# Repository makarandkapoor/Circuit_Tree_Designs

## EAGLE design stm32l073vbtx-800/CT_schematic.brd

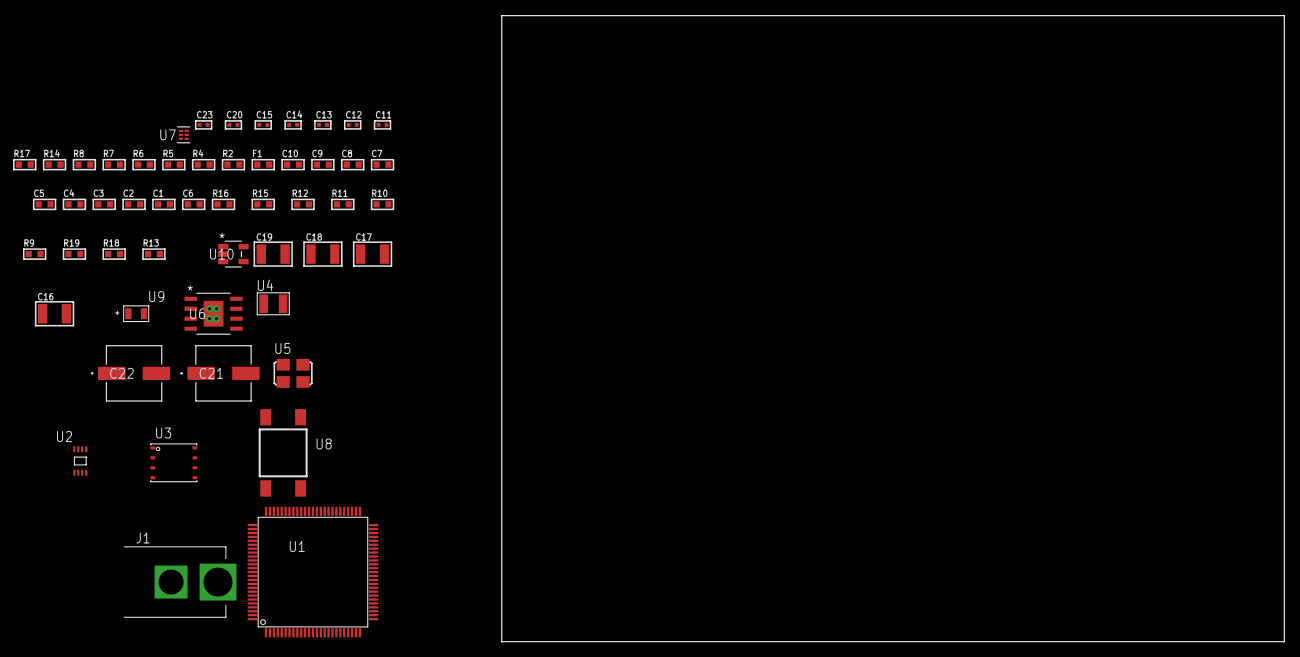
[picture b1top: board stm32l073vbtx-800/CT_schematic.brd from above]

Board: 2 copper layers, 100.0 x 80.0 mm, 52 parts (0 on the bottom side), 23 nets, no tracks yet.

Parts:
C1, C2, C3, C4, C5, C7, C10: 1e-07; C0603
C6: 4.7e-06; C0603
C8: 1e-08; C0603
C9: 1e-06; C0603
C11, C12: 1e-11; C0402
C13, C14, C15, C23: 1e-08; C0402
C16, C17, C18, C19: 1e-05; C1210
C20: 1e-07; C0402
C21, C22: 0.0001; EXV-9H
F1: 240.0; L0603
J1: PJ-037B; PJ-037B_PACKAGE
R2: 1000.0; R0603
R4: 4700.0; R0603
R5, R6, R7, R8, R14: 2200.0; R0603
R9, R10, R11, R12, R15, R16: 10000.0; R0603
R13: 4031.5447154472; R0603
R17: 9100.0; R0603
R18: 680000.0; R0603
R19: 120000.0; R0603
U1: STM32L073VBT6; LQFP100
U2: 24AA04-I/MC; TDFN-8/6MM
U3: 24AA256-I/MF; DFN8-S
U4: ABS07-32.768KHZ-7-T
U5: ASFL1-25MHZ-NCS; ASFL1
U6: MIC5234YME; SOIC-8_EP
U7: TPS3895ADRYR; SON-6
U8: 4-1437565-2; SW_4-1437565-2
U9: Q65110A2395; LGM67K-G1J2-24-Z
U10: nc7sz125m5x; NC7SZ125M5X

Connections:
CLK_CRYSTAL_U1_8: C11.1, U1.8, U4.1
CLK_CRYSTAL_U1_9: C12.1, U1.9, U4.2
CLK_U1_12: U1.12, U5.3
GND: C1.2, C2.2, C3.2, C4.2, C5.2, C6.2, C7.2, C8.2, C9.2, C10.2, C11.2, C12.2, C13.2, C14.2, C15.2, C16.2, C17.2, C18.2, C19.2, C20.2, C21.2, C22.2, C23.2, J1.2, R2.2, R9.2, R10.2, R12.2, R14.2, R17.2, R19.2, U1.19, U1.20, U1.27, U1.49, U1.74, U1.99, U2.4, U3.4, U5.2, U6.7, U6.EPAD, U7.2, U9.C, U10.1, U10.3
NET_U1_6: C7.1, U1.6
NET_U1_14: R4.1, U1.14, U10.4
NET_U1_22: C8.1, C9.1, F1.1, U1.21, U1.22
NET_U1_47: R7.1, U1.47, U2.6
NET_U1_48: R8.1, U1.48, U2.5
NET_U1_68: R5.1, U1.68, U3.6
NET_U1_69: R6.1, U1.69, U3.5
NET_U1_94: R9.1, U1.94
NET_U1_98: U8.3, U8.4
NET_U3_1: R10.1, U3.1
NET_U3_2: R11.1, U3.2
NET_U3_3: R12.1, U3.3
NET_U6_4: R13.2, R14.1, U6.4
NET_U7_1: R16.1, R17.1, U7.1
NET_U7_3: R18.2, R19.1, U7.3
NET_U7_4: R15.1, U7.4, U10.2
NET_U8_1: R2.1, U8.1, U8.2
VCC_S1_13V7: C16.1, C17.1, C21.1, C22.1, J1.1, U6.5, U6.8
VCC_TIER1_3V3: C1.1, C2.1, C3.1, C4.1, C5.1, C6.1, C10.1, C13.1, C14.1, C15.1, C18.1, C19.1, C20.1, C23.1, F1.2, R4.2, R5.2, R6.2, R7.2, R8.2, R11.2, R13.1, R15.2, R16.2, R18.1, U1.28, U1.50, U1.73, U1.75, U1.100, U2.7, U2.8, U3.7, U3.8, U5.4, U6.1, U7.6, U10.5

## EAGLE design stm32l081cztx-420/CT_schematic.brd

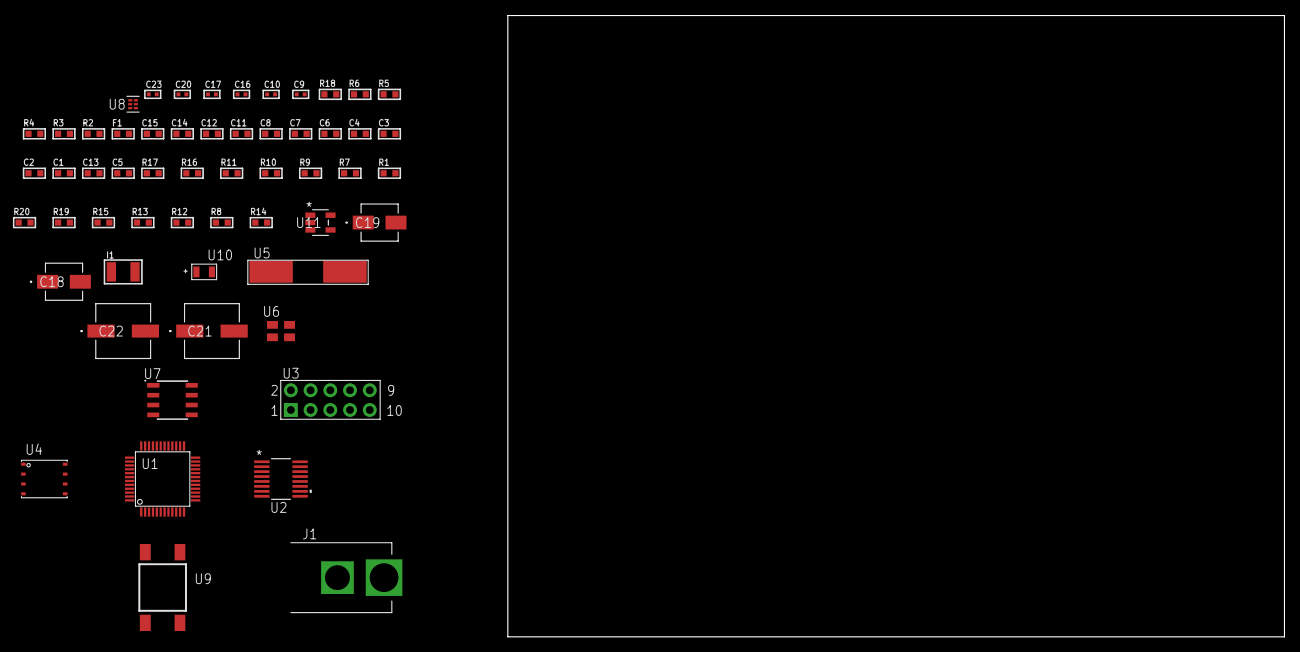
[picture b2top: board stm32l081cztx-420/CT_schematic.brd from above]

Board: 2 copper layers, 100.0 x 80.0 mm, 57 parts (0 on the bottom side), 36 nets, no tracks yet.

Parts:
C1, C2, C3, C4, C6: 1e-07; C0603
C5: 4.7e-06; C0603
C7: 1e-08; C0603
C8, C11, C12, C14, C15: 1e-06; C0603
C9, C10: 1e-11; C0402
C13: 2.2e-07; C0603
C16, C17, C23: 1e-08; C0402
C18: 1e-06; EXV-9B
C19: 2.2e-06; EXV-9B
C20: 1e-07; C0402
C21, C22: 0.0001; EXV-9H
F1: 240.0; L0603
I1: 1e-05; L1210
J1: PJ-037B; PJ-037B_PACKAGE
R1, R7, R9, R10, R11, R16, R17: 10000.0; R0603
R2: 1000.0; R0603
R3: 1600.5; R0603
R4: 4700.0; R0603
R5, R6: 2200.0; R0603
R8, R12, R13, R15: 100000.0; R0603
R14: 164658.62; R0603
R18: 9100.0; R0603
R19: 680000.0; R0603
R20: 120000.0; R0603
U1: STM32L081CZT6; LQFP48
U2: LTC2804CGN-1#PBF; SSOP-16
U3: HTSS-105-01-G-D
U4: 24AA256-I/MF; DFN8-S
U5: ABLS-25.000MHZ-B2F-T
U6: ASEK-32.768KHz-ECST; ASEK
U7: LP2954AIMX/NOPB; LP2954
U8: TPS3895ADRYR; SON-6
U9: 4-1437565-2; SW_4-1437565-2
U10: Q65110A2395; LGM67K-G1J2-24-Z
U11: nc7sz125m5x; NC7SZ125M5X

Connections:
CLK_CRYSTAL_U1_5: C9.1, U1.5, U5.1
CLK_CRYSTAL_U1_6: C10.1, U1.6, U5.2
CLK_U1_3: U1.3, U6.3
GND: C1.2, C2.2, C3.2, C4.2, C5.2, C6.2, C7.2, C8.2, C9.2, C10.2, C11.2, C12.2, C14.2, C15.2, C16.2, C17.2, C18.2, C19.2, C20.2, C21.2, C22.2, C23.2, J1.2, R2.2, R7.2, R9.2, R10.2, R15.2, R18.2, R20.2, U1.8, U1.23, U1.35, U1.47, U2.8, U3.9, U4.4, U6.2, U7.4, U8.2, U10.C, U11.1, U11.3
NET_U1_7: R4.1, U1.7, U11.4
NET_U1_9: C7.1, C8.1, F1.1, U1.9
NET_U1_30: R5.1, U1.30, U4.6
NET_U1_31: R6.1, U1.31, U4.5
NET_U1_44: R7.1, U1.44
NET_U1_45: R3.1, U1.45, U10.A
NET_U1_46: R1.1, U1.46, U9.3, U9.4
NET_U2_6: C11.1, U2.6
NET_U2_7: C13.1, I1.2, U2.7
NET_U2_9: C12.1, U2.9
NET_U2_10: C13.2, U2.10
NET_U2_11: R8.1, U2.11
NET_U3_3: U2.1, U3.3
NET_U3_4: U2.2, U3.4
NET_U3_5: U2.3, U3.5
NET_U3_6: U2.4, U3.6
NET_U4_1: R9.1, U4.1
NET_U4_2: R10.1, U4.2
NET_U4_3: R11.1, U4.3
NET_U7_3: R13.1, U7.3
NET_U7_5: R12.1, U7.5
NET_U7_7: R14.2, R15.1, U7.7
NET_U8_1: R17.1, R18.1, U8.1
NET_U8_3: R19.2, R20.1, U8.3
NET_U8_4: R16.1, U8.4, U11.2
NET_U9_1: R2.1, U9.1, U9.2
PROC_LPUART1_CTS: U1.16, U2.13
PROC_LPUART1_RTS: U1.19, U2.15
PROC_LPUART1_RX: U1.13, U2.16
PROC_LPUART1_TX: U1.12, U2.14
VCC_S1_16V4: C18.1, C21.1, C22.1, J1.1, R13.2, U7.8
VCC_TIER1_3V3: C1.1, C2.1, C3.1, C4.1, C5.1, C6.1, C14.1, C15.1, C16.1, C17.1, C19.1, C20.1, C23.1, F1.2, I1.1, R1.2, R3.2, R4.2, R5.2, R6.2, R8.2, R11.2, R12.2, R14.1, R16.2, R17.2, R19.1, U1.1, U1.24, U1.36, U1.48, U2.5, U2.12, U4.7, U4.8, U6.4, U7.1, U8.6, U11.5

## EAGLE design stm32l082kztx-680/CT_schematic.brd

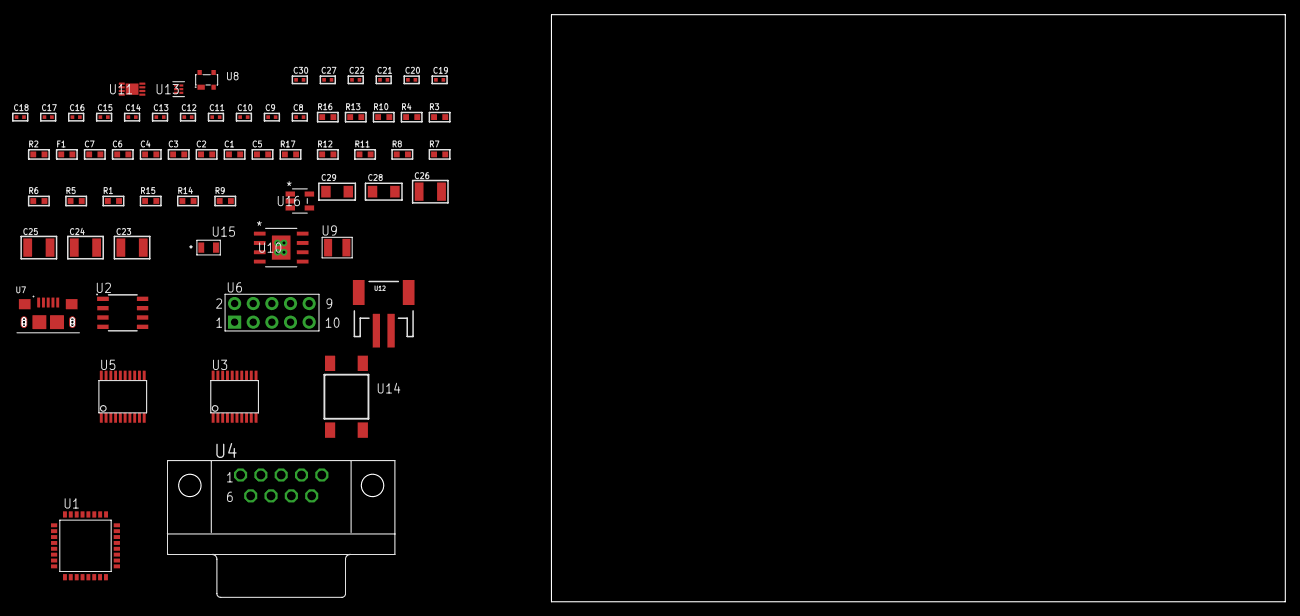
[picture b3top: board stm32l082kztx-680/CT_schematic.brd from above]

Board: 2 copper layers, 172.1 x 80.0 mm, 64 parts (0 on the bottom side), 54 nets, no tracks yet.

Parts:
C1, C2, C3, C4: 1e-07; C0603
C5: 4.7e-06; C0603
C6: 1e-08; C0603
C7: 1e-06; C0603
C8, C9: 1e-11; C0402
C10, C30: 1e-08; C0402
C11, C12, C13, C14, C15, C16, C17, C18, C19, C20, C21, C22, C27: 1e-07; C0402
C23, C24, C25, C26: 1e-05; C1210
C28, C29: 1e-05; C1206
F1: 240.0; L0603
R1, R5, R6, R7, R8, R11, R12, R17: 10000.0; R0603
R2: 1000.0; R0603
R3: 1600.5; R0603
R4: 4700.0; R0603
R9: 4031.5447154472; R0603
R10: 2200.0; R0603
R13: 9100.0; R0603
R14: 680000.0; R0603
R15: 120000.0; R0603
R16: 2000.0; R0603
U1: STM32L082KZT6; LQFP32
U2: AT25020B-SSHL-T; SOIC-8
U3, U5: SP3203ECY-L/TR; TSSOP20-I
U4: 182-009-113R531; 182-009-MALE
U6: HTSS-105-01-G-D
U7: 10118193-0001LF; FCI_10118193-0001LF
U8: prtr5v0u2ax; SOT143B
U9: ABS07-32.768KHZ-7-T
U10: MIC5234YME; SOIC-8_EP
U11: MCP73831T-2ACI/MC; DFN8_2X3MC
U12: S2B-PH-SM4-TB(LF)(SN); JST-2-SMD
U13: TPS3895ADRYR; SON-6
U14: 4-1437565-2; SW_4-1437565-2
U15: Q65110A2395; LGM67K-G1J2-24-Z
U16: nc7sz125m5x; NC7SZ125M5X

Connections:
CLK_CRYSTAL_U1_2: C8.1, U1.2, U9.1
CLK_CRYSTAL_U1_3: C9.1, U1.3, U9.2
GND: C1.2, C2.2, C3.2, C4.2, C5.2, C6.2, C7.2, C8.2, C9.2, C10.2, C11.2, C12.2, C15.2, C16.2, C17.2, C18.2, C21.2, C22.2, C23.2, C24.2, C25.2, C26.2, C27.2, C28.2, C29.2, C30.2, R2.2, R5.2, R10.2, R13.2, R15.2, R16.2, U1.16, U1.32, U2.4, U3.18, U4.5, U5.18, U6.9, U7.5, U7.6, U7.7, U7.8, U7.9, U8.1, U10.7, U10.EPAD, U11.6, U11.9, U12.2, U13.2, U15.C, U16.1, U16.3
INPUT_USBPOWER_5V: C28.1, R17.2, U7.1, U8.4, U11.1, U11.2
NET_U1_4: R4.1, U1.4, U16.4
NET_U1_5: C6.1, C7.1, F1.1, U1.5
NET_U1_29: R3.1, U1.29, U15.A
NET_U1_30: R1.1, U1.30, U14.3, U14.4
NET_U1_31: R5.1, U1.31
NET_U2_3: R6.1, U2.3
NET_U2_7: R8.1, U2.7
NET_U3_1: C13.1, U3.1
NET_U3_2: C15.1, U3.2
NET_U3_3: C13.2, U3.3
NET_U3_4: C14.1, U3.4
NET_U3_5: C14.2, U3.5
NET_U3_6: C16.1, U3.6
NET_U4_2: U3.14, U4.2
NET_U4_3: U3.17, U4.3
NET_U4_7: U3.13, U4.7
NET_U4_8: U3.16, U4.8
NET_U5_1: C19.1, U5.1
NET_U5_2: C21.1, U5.2
NET_U5_3: C19.2, U5.3
NET_U5_4: C20.1, U5.4
NET_U5_5: C20.2, U5.5
NET_U5_6: C22.1, U5.6
NET_U6_3: U5.14, U6.3
NET_U6_4: U5.13, U6.4
NET_U6_5: U5.17, U6.5
NET_U6_6: U5.16, U6.6
NET_U10_4: R9.2, R10.1, U10.4
NET_U11_5: R17.1, U11.5
NET_U11_8: R16.1, U11.8
NET_U13_1: R12.1, R13.1, U13.1
NET_U13_3: R14.2, R15.1, U13.3
NET_U13_4: R11.1, U13.4, U16.2
NET_U14_1: R2.1, U14.1, U14.2
PROC_LPUART1_CTS: U1.12, U3.8
PROC_LPUART1_RTS: U1.15, U3.10
PROC_LPUART1_RX: U1.9, U3.11
PROC_LPUART1_TX: U1.8, U3.7
PROC_SPI1_MISO: U1.27, U2.2
PROC_SPI1_MOSI: U1.13, U2.5
PROC_SPI1_NSS: R7.1, U1.10, U2.1
PROC_SPI1_SCK: U1.11, U2.6
PROC_USART2_CTS: U1.6, U5.8
PROC_USART2_RTS: U1.7, U5.10
PROC_USART2_RX: U1.25, U5.11
PROC_USART2_TX: U1.24, U5.7
PROC_USB_DM: U1.21, U7.2, U8.3
PROC_USB_DP: U1.22, U7.3, U8.2
VCC_S1_3V7: C23.1, C24.1, C29.1, U10.5, U10.8, U11.3, U11.4, U12.1
VCC_TIER1_3V3: C1.1, C2.1, C3.1, C4.1, C5.1, C10.1, C11.1, C12.1, C17.1, C18.1, C25.1, C26.1, C27.1, C30.1, F1.2, R1.2, R3.2, R4.2, R6.2, R7.2, R8.2, R9.1, R11.2, R12.2, R14.1, U1.1, U1.17, U2.8, U3.12, U3.19, U5.12, U5.19, U10.1, U13.6, U16.5

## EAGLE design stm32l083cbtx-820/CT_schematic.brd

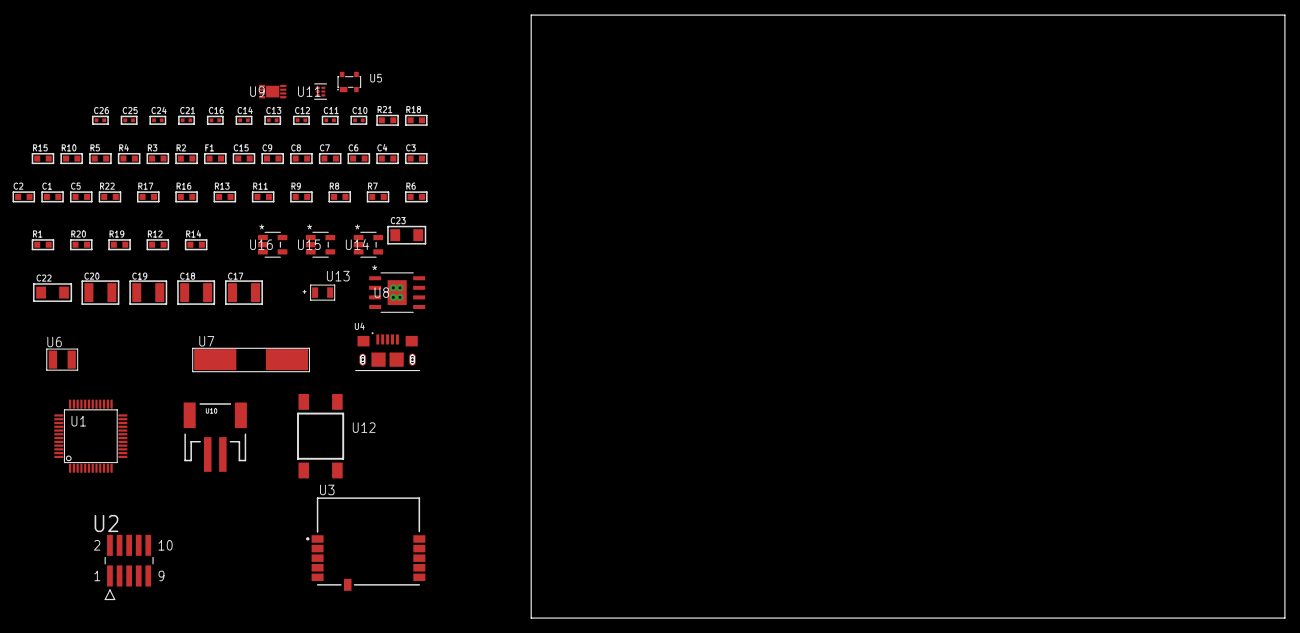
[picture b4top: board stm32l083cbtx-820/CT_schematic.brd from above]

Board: 2 copper layers, 122.6 x 80.0 mm, 65 parts (0 on the bottom side), 33 nets, no tracks yet.

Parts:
C1, C2, C3, C4, C6, C9: 1e-07; C0603
C5: 4.7e-06; C0603
C7: 1e-08; C0603
C8, C15: 1e-06; C0603
C10, C11, C12, C13: 1e-11; C0402
C14, C16, C21: 1e-07; C0402
C17, C18, C19, C20: 1e-05; C1210
C22, C23: 1e-05; C1206
C24, C25, C26: 1e-08; C0402
F1: 240.0; L0603
R1, R6, R7, R8, R9, R11, R16, R17, R22: 10000.0; R0603
R2: 1000.0; R0603
R3: 1600.5; R0603
R4, R5: 4700.0; R0603
R10: 5.0; R0603
R12: 100000.0; R0603
R13: 47000.0; R0603
R14: 4031.5447154472; R0603
R15: 2200.0; R0603
R18: 9100.0; R0603
R19: 680000.0; R0603
R20: 120000.0; R0603
R21: 2000.0; R0603
U1: STM32L083CBT6; LQFP48
U2: FTSH-105-01-L-DV-K; SAMTEC_FTSH-105-01-L-DV-K
U3: SPBTLE-RF; XCVR_SPBTLE-RF
U4: 10118193-0001LF; FCI_10118193-0001LF
U5: prtr5v0u2ax; SOT143B
U6: ABS07-32.768KHZ-7-T
U7: ABLS-25.000MHZ-B2F-T
U8: MIC5234YME; SOIC-8_EP
U9: MCP73831T-2ACI/MC; DFN8_2X3MC
U10: S2B-PH-SM4-TB(LF)(SN); JST-2-SMD
U11: TPS3895ADRYR; SON-6
U12: 4-1437565-2; SW_4-1437565-2
U13: Q65110A2395; LGM67K-G1J2-24-Z
U14, U15, U16: nc7sz125m5x; NC7SZ125M5X

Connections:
CLK_CRYSTAL_U1_3: C10.1, U1.3, U6.1
CLK_CRYSTAL_U1_4: C11.1, U1.4, U6.2
CLK_CRYSTAL_U1_5: C12.1, U1.5, U7.1
CLK_CRYSTAL_U1_6: C13.1, U1.6, U7.2
GND: C1.2, C2.2, C3.2, C4.2, C5.2, C6.2, C7.2, C8.2, C9.2, C10.2, C11.2, C12.2, C13.2, C14.2, C15.2, C16.2, C17.2, C18.2, C19.2, C20.2, C21.2, C22.2, C23.2, C24.2, C25.2, C26.2, R2.2, R6.2, R10.2, R12.2, R13.2, R15.2, R18.2, R20.2, R21.2, U1.8, U1.23, U1.35, U1.47, U2.3, U2.5, U3.6, U4.5, U4.6, U4.7, U4.8, U4.9, U5.1, U8.7, U8.EPAD, U9.6, U9.9, U10.2, U11.2, U13.C, U14.2, U14.3, U15.1, U15.3, U16.1, U16.3
INPUT_USBPOWER_5V: C22.1, R22.2, U4.1, U5.4, U9.1, U9.2
NET_U1_1: C6.1, U1.1
NET_U1_7: R5.1, U1.7, U16.4
NET_U1_9: C7.1, C8.1, F1.1, U1.9
NET_U1_44: R6.1, U1.44
NET_U1_45: R3.1, U1.45, U13.A
NET_U1_46: R1.1, U1.46, U12.3, U12.4
NET_U2_9: R10.1, U2.9
NET_U3_11: R4.1, U3.11, U15.4
NET_U8_4: R14.2, R15.1, U8.4
NET_U9_5: R22.1, U9.5
NET_U9_8: R21.1, U9.8
NET_U11_1: R17.1, R18.1, U11.1
NET_U11_3: R19.2, R20.1, U11.3
NET_U11_4: R16.1, U11.4, U14.4, U15.2, U16.2
NET_U12_1: R2.1, U12.1, U12.2
PROC_GPIO_TO_U3_SPI_IRQ: R13.1, U1.2, U3.4
PROC_SPI1_MISO: U1.16, U3.8
PROC_SPI1_MOSI: U1.17, U3.9
PROC_SPI1_NSS: R11.1, U1.14, U3.10
PROC_SPI1_SCK: R12.1, U1.15, U3.7
PROC_SYS_SWCLK: R8.1, U1.37, U2.4
PROC_SYS_SWDIO: R9.1, U1.34, U2.2
PROC_USB_DM: U1.32, U4.2, U5.3
PROC_USB_DP: U1.33, U4.3, U5.2
RST_OUT_U2_JTAG_RST_B: R7.1, U2.10, U14.1
VCC_S1_3V7: C17.1, C18.1, C23.1, U8.5, U8.8, U9.3, U9.4, U10.1
VCC_TIER1_3V3: C1.1, C2.1, C3.1, C4.1, C5.1, C9.1, C14.1, C15.1, C16.1, C19.1, C20.1, C21.1, C24.1, C25.1, C26.1, F1.2, R1.2, R3.2, R4.2, R5.2, R7.2, R8.2, R9.2, R11.2, R14.1, R16.2, R17.2, R19.1, U1.24, U1.36, U1.48, U2.1, U3.5, U8.1, U11.6, U14.5, U15.5, U16.5

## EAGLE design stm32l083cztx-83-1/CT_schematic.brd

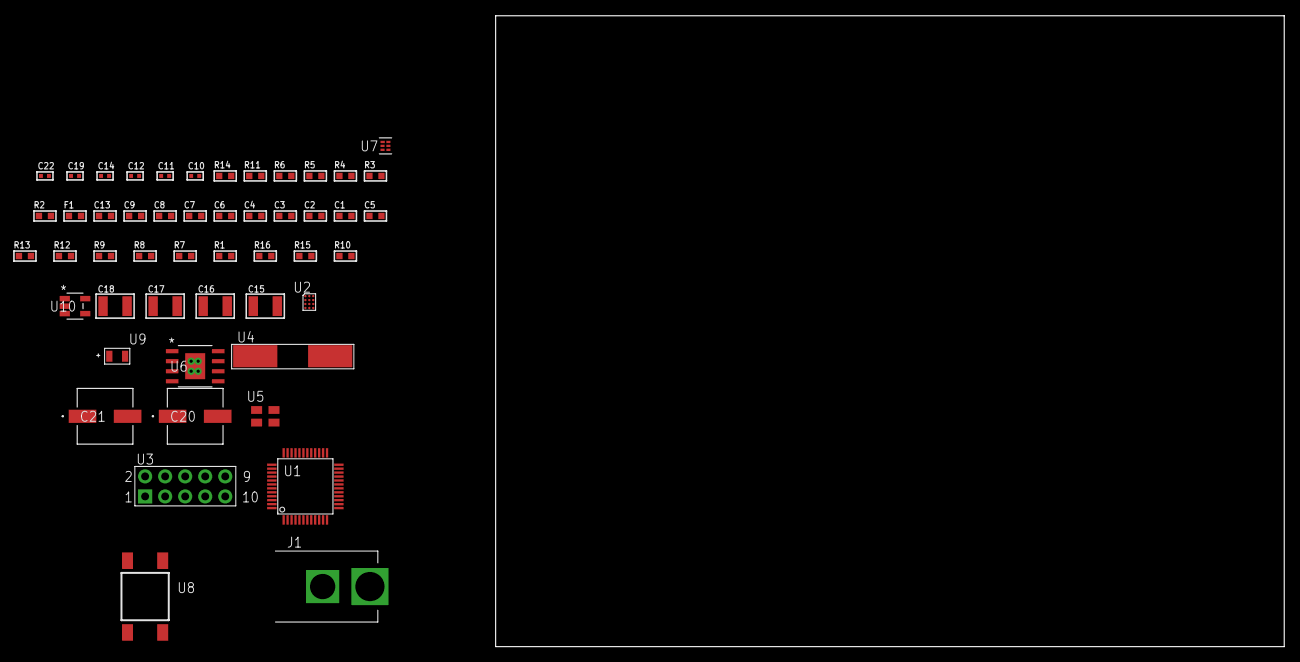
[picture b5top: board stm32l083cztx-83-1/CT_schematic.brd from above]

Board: 2 copper layers, 100.0 x 80.0 mm, 50 parts (0 on the bottom side), 25 nets, no tracks yet.

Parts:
C1, C2, C3, C4, C6, C9: 1e-07; C0603
C5: 4.7e-06; C0603
C7: 1e-08; C0603
C8, C13: 1e-06; C0603
C10, C11: 1e-11; C0402
C12, C19: 1e-07; C0402
C14, C22: 1e-08; C0402
C15, C16, C17, C18: 1e-05; C1210
C20, C21: 0.0001; EXV-9H
F1: 240.0; L0603
J1: PJ-037B; PJ-037B_PACKAGE
R1, R7, R8, R9, R12, R13: 10000.0; R0603
R2: 1000.0; R0603
R3: 1600.5; R0603
R4: 4700.0; R0603
R5, R6, R11: 2200.0; R0603
R10: 4031.5447154472; R0603
R14: 9100.0; R0603
R15: 680000.0; R0603
R16: 120000.0; R0603
U1: STM32L083CZT6; LQFP48
U2: TSC2014IYZGT
U3: HTSS-105-01-G-D
U4: ABLS-25.000MHZ-B2F-T
U5: ASEK-32.768KHz-ECST; ASEK
U6: MIC5234YME; SOIC-8_EP
U7: TPS3895ADRYR; SON-6
U8: 4-1437565-2; SW_4-1437565-2
U9: Q65110A2395; LGM67K-G1J2-24-Z
U10: nc7sz125m5x; NC7SZ125M5X

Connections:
CLK_CRYSTAL_U1_5: C10.1, U1.5, U4.1
CLK_CRYSTAL_U1_6: C11.1, U1.6, U4.2
CLK_U1_3: U1.3, U5.3
GND: C1.2, C2.2, C3.2, C4.2, C5.2, C6.2, C7.2, C8.2, C9.2, C10.2, C11.2, C12.2, C13.2, C14.2, C15.2, C16.2, C17.2, C18.2, C19.2, C20.2, C21.2, C22.2, J1.2, R2.2, R7.2, R11.2, R14.2, R16.2, U1.8, U1.23, U1.35, U1.47, U2.D2, U3.9, U5.2, U6.7, U6.EPAD, U7.2, U9.C, U10.1, U10.3
NET_U1_1: C6.1, U1.1
NET_U1_7: R4.1, U1.7, U10.4
NET_U1_9: C7.1, C8.1, F1.1, U1.9
NET_U1_30: R5.1, U1.30, U2.D1
NET_U1_31: R6.1, U1.31, U2.C1
NET_U1_44: R7.1, U1.44
NET_U1_45: R3.1, U1.45, U9.A
NET_U1_46: R1.1, U1.46, U8.3, U8.4
NET_U2_B1: R9.1, U2.B1
NET_U2_C2: R8.1, U2.C2
NET_U3_3: U2.B3, U3.3
NET_U3_4: U2.D3, U3.4
NET_U3_5: U2.A3, U3.5
NET_U3_6: U2.C3, U3.6
NET_U6_4: R10.2, R11.1, U6.4
NET_U7_1: R13.1, R14.1, U7.1
NET_U7_3: R15.2, R16.1, U7.3
NET_U7_4: R12.1, U7.4, U10.2
NET_U8_1: R2.1, U8.1, U8.2
VCC_S1_14V6: C15.1, C16.1, C20.1, C21.1, J1.1, U6.5, U6.8
VCC_TIER1_3V3: C1.1, C2.1, C3.1, C4.1, C5.1, C9.1, C12.1, C13.1, C14.1, C17.1, C18.1, C19.1, C22.1, F1.2, R1.2, R3.2, R4.2, R5.2, R6.2, R8.2, R9.2, R10.1, R12.2, R13.2, R15.1, U1.24, U1.36, U1.48, U2.A2, U2.B2, U5.4, U6.1, U7.6, U10.5

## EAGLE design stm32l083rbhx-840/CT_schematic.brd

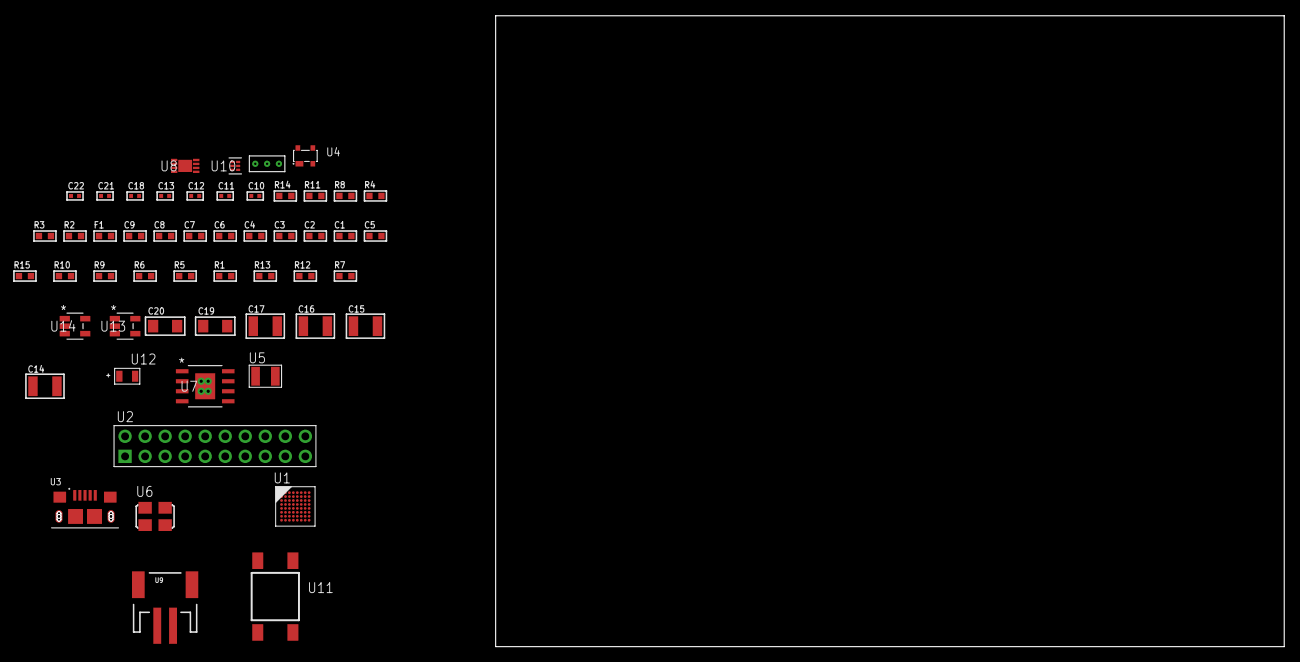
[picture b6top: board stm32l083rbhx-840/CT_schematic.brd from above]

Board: 2 copper layers, 155.6 x 80.0 mm, 53 parts (0 on the bottom side), 27 nets, no tracks yet.

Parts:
C1, C2, C3, C4, C6, C9: 1e-07; C0603
C5: 4.7e-06; C0603
C7: 1e-08; C0603
C8: 1e-06; C0603
C10, C11: 1e-11; C0402
C12, C18: 1e-07; C0402
C13, C21, C22: 1e-08; C0402
C14, C15, C16, C17: 1e-05; C1210
C19, C20: 1e-05; C1206
F1: 240.0; L0603
R1, R5, R6, R9, R10, R15: 10000.0; R0603
R2: 1000.0; R0603
R3: 1600.5; R0603
R4: 4700.0; R0603
R7: 4031.5447154472; R0603
R8: 2200.0; R0603
R11: 9100.0; R0603
R12: 680000.0; R0603
R13: 120000.0; R0603
R14: 2000.0; R0603
U1: STM32L083RBH6; TFBGA64
U2: TST-110-05-T-D-RA
U3: 10118193-0001LF; FCI_10118193-0001LF
U4: prtr5v0u2ax; SOT143B
U5: ABS07-32.768KHZ-7-T
U6: ASFL1-25MHZ-NCS; ASFL1
U7: MIC5234YME; SOIC-8_EP
U8: MCP73831T-2ACI/MC; DFN8_2X3MC
U9: S2B-PH-SM4-TB(LF)(SN); JST-2-SMD
U10: TPS3895ADRYR; SON-6
U11: 4-1437565-2; SW_4-1437565-2
U12: Q65110A2395; LGM67K-G1J2-24-Z
U13, U14: nc7sz125m5x; NC7SZ125M5X
U15: Dummy; DUMMY_PACKAGE_116

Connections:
CLK_CRYSTAL_U1_A1: C10.1, U1.A1, U5.1
CLK_CRYSTAL_U1_B1: C11.1, U1.B1, U5.2
CLK_U1_C1: U1.C1, U6.3
GND: C1.2, C2.2, C3.2, C4.2, C5.2, C6.2, C7.2, C8.2, C9.2, C10.2, C11.2, C12.2, C13.2, C14.2, C15.2, C16.2, C17.2, C18.2, C19.2, C20.2, C21.2, C22.2, R2.2, R5.2, R8.2, R11.2, R13.2, R14.2, U1.C2, U1.D4, U1.D5, U1.D6, U1.F1, U2.4, U2.6, U2.8, U2.10, U2.12, U2.14, U2.16, U2.18, U2.20, U3.5, U3.6, U3.7, U3.8, U3.9, U4.1, U6.2, U7.7, U7.EPAD, U8.6, U8.9, U9.2, U10.2, U12.C, U13.2, U13.3, U14.1, U14.3, U15.1
INPUT_USBPOWER_5V: C19.1, R15.2, U3.1, U4.4, U8.1, U8.2
NET_U1_B2: C6.1, U1.B2
NET_U1_B4: R5.1, U1.B4
NET_U1_E1: R4.1, U1.E1, U14.4
NET_U1_H1: C7.1, C8.1, F1.1, U1.G1, U1.H1
NET_U1_H7: R3.1, U1.H7, U12.A
NET_U1_H8: R1.1, U1.H8, U11.3, U11.4
NET_U7_4: R7.2, R8.1, U7.4
NET_U8_5: R15.1, U8.5
NET_U8_8: R14.1, U8.8
NET_U10_1: R10.1, R11.1, U10.1
NET_U10_3: R12.2, R13.1, U10.3
NET_U10_4: R9.1, U10.4, U13.4, U14.2
NET_U11_1: R2.1, U11.1, U11.2
PROC_ADC_IN3: U1.G3, U15.2
PROC_ADC_IN4: U1.H3, U15.3
PROC_SYS_SWCLK: U1.A7, U2.9
PROC_SYS_SWDIO: U1.A8, U2.7
PROC_USB_DM: U1.C8, U3.2, U4.3
PROC_USB_DP: U1.B8, U3.3, U4.2
RST_OUT_U2_SRESET_B: R6.1, U2.15, U13.1
VCC_S1_3V7: C14.1, C15.1, C20.1, U7.5, U7.8, U8.3, U8.4, U9.1
VCC_TIER1_3V3: C1.1, C2.1, C3.1, C4.1, C5.1, C9.1, C12.1, C13.1, C16.1, C17.1, C18.1, C21.1, C22.1, F1.2, R1.2, R3.2, R4.2, R6.2, R7.1, R9.2, R10.2, R12.1, U1.D2, U1.E4, U1.E5, U1.E6, U2.1, U6.4, U7.1, U10.6, U13.5, U14.5

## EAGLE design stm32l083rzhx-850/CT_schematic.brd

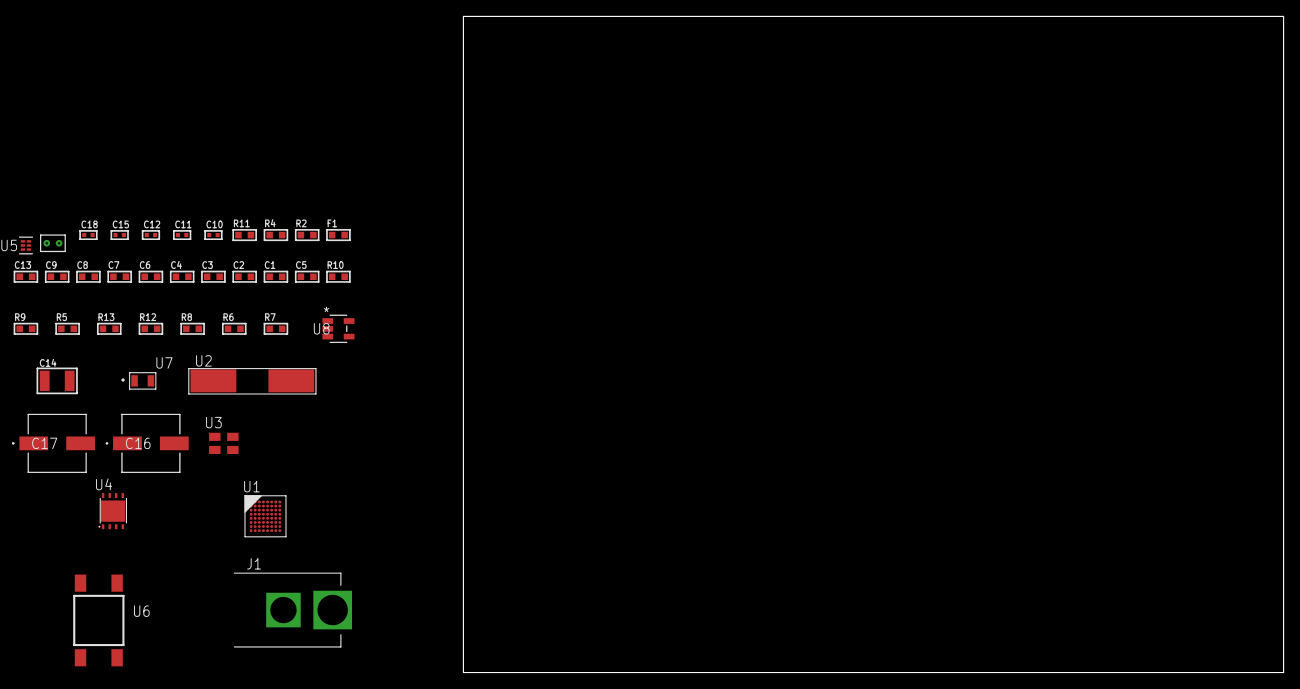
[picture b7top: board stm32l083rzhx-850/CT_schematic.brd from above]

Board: 2 copper layers, 100.0 x 80.0 mm, 40 parts (0 on the bottom side), 18 nets, no tracks yet.

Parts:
C1, C2, C3, C4, C6, C9: 1e-07; C0603
C5: 4.7e-06; C0603
C7: 1e-08; C0603
C8, C13: 1e-06; C0603
C10, C11: 1e-11; C0402
C12, C18: 1e-08; C0402
C14: 1e-05; C1210
C15: 1e-07; C0402
C16, C17: 0.0001; EXV-9H
F1: 240.0; L0603
J1: PJ-037B; PJ-037B_PACKAGE
R2: 1000.0; R0603
R4: 4700.0; R0603
R5, R9, R10: 10000.0; R0603
R6, R8: 100000.0; R0603
R7: 153694.38; R0603
R11: 9100.0; R0603
R12: 680000.0; R0603
R13: 120000.0; R0603
U1: STM32L083RZH6; TFBGA64
U2: ABLS-25.000MHZ-B2F-T
U3: ASEK-32.768KHz-ECST; ASEK
U4: LP2951ACSDX/NOPB; WSON-8
U5: TPS3895ADRYR; SON-6
U6: 4-1437565-2; SW_4-1437565-2
U7: Q65110A2395; LGM67K-G1J2-24-Z
U8: nc7sz125m5x; NC7SZ125M5X
U9: Dummy; DUMMY_PACKAGE_82

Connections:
CLK_CRYSTAL_U1_C1: C10.1, U1.C1, U2.1
CLK_CRYSTAL_U1_D1: C11.1, U1.D1, U2.2
CLK_U1_A1: U1.A1, U3.3
GND: C1.2, C2.2, C3.2, C4.2, C5.2, C6.2, C7.2, C8.2, C9.2, C10.2, C11.2, C12.2, C13.2, C14.2, C15.2, C16.2, C17.2, C18.2, J1.2, R2.2, R5.2, R8.2, R11.2, R13.2, U1.C2, U1.D4, U1.D5, U1.D6, U1.F1, U3.2, U4.3, U4.4, U4.PAD, U5.2, U7.C, U8.1, U8.3, U9.1
NET_U1_B2: C6.1, U1.B2
NET_U1_B4: R5.1, U1.B4
NET_U1_E1: R4.1, U1.E1, U8.4
NET_U1_H1: C7.1, C8.1, F1.1, U1.G1, U1.H1
NET_U1_H8: U6.3, U6.4
NET_U4_5: R6.1, U4.5
NET_U4_7: R7.2, R8.1, U4.7
NET_U5_1: R10.1, R11.1, U5.1
NET_U5_3: R12.2, R13.1, U5.3
NET_U5_4: R9.1, U5.4, U8.2
NET_U6_1: R2.1, U6.1, U6.2
PROC_DAC_OUT2: U1.F4, U9.2
VCC_S1_5V9: C13.1, C16.1, C17.1, J1.1, U4.8
VCC_TIER1_3V3: C1.1, C2.1, C3.1, C4.1, C5.1, C9.1, C12.1, C14.1, C15.1, C18.1, F1.2, R4.2, R6.2, R7.1, R9.2, R10.2, R12.1, U1.D2, U1.E4, U1.E5, U1.E6, U3.4, U4.1, U5.6, U8.5

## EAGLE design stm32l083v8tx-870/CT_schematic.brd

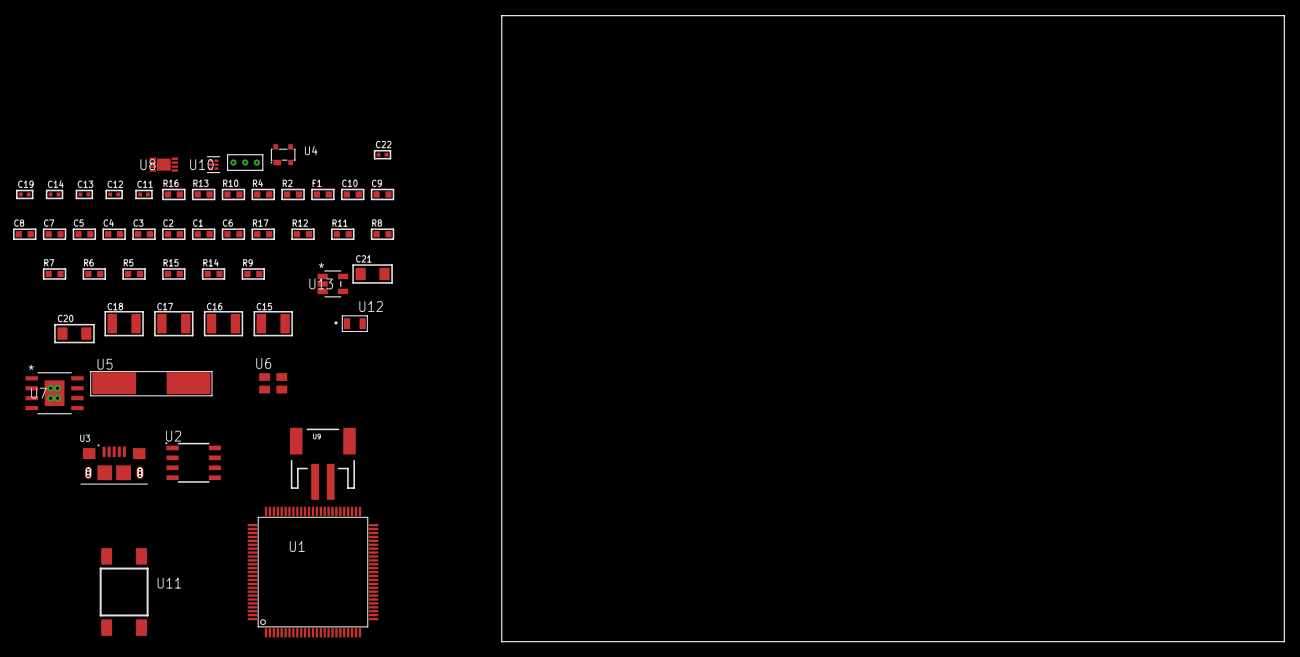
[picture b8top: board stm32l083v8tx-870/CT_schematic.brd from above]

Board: 2 copper layers, 153.1 x 80.0 mm, 52 parts (0 on the bottom side), 29 nets, no tracks yet.

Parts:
C1, C2, C3, C4, C5, C7, C10: 1e-07; C0603
C6: 4.7e-06; C0603
C8: 1e-08; C0603
C9: 1e-06; C0603
C11, C12: 1e-11; C0402
C13, C14, C22: 1e-08; C0402
C15, C16, C17, C18: 1e-05; C1210
C19: 1e-07; C0402
C20, C21: 1e-05; C1206
F1: 240.0; L0603
R2: 1000.0; R0603
R4: 4700.0; R0603
R5, R6, R7, R8, R11, R12, R17: 10000.0; R0603
R9: 4031.5447154472; R0603
R10: 2200.0; R0603
R13: 9100.0; R0603
R14: 680000.0; R0603
R15: 120000.0; R0603
R16: 2000.0; R0603
U1: STM32L083V8T6; LQFP100
U2: AT25320B-SSHL-T; SOIC-8
U3: 10118193-0001LF; FCI_10118193-0001LF
U4: prtr5v0u2ax; SOT143B
U5: ABLS-25.000MHZ-B2F-T
U6: ASEK-32.768KHz-ECST; ASEK
U7: MIC5234YME; SOIC-8_EP
U8: MCP73831T-2ACI/MC; DFN8_2X3MC
U9: S2B-PH-SM4-TB(LF)(SN); JST-2-SMD
U10: TPS3895ADRYR; SON-6
U11: 4-1437565-2; SW_4-1437565-2
U12: Q65110A2395; LGM67K-G1J2-24-Z
U13: nc7sz125m5x; NC7SZ125M5X
U14: Dummy; DUMMY_PACKAGE_115

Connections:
CLK_CRYSTAL_U1_12: C11.1, U1.12, U5.1
CLK_CRYSTAL_U1_13: C12.1, U1.13, U5.2
CLK_U1_8: U1.8, U6.3
GND: C1.2, C2.2, C3.2, C4.2, C5.2, C6.2, C7.2, C8.2, C9.2, C10.2, C11.2, C12.2, C13.2, C14.2, C15.2, C16.2, C17.2, C18.2, C19.2, C20.2, C21.2, C22.2, R2.2, R5.2, R10.2, R13.2, R15.2, R16.2, U1.19, U1.20, U1.27, U1.49, U1.74, U1.99, U2.4, U3.5, U3.6, U3.7, U3.8, U3.9, U4.1, U6.2, U7.7, U7.EPAD, U8.6, U8.9, U9.2, U10.2, U12.C, U13.1, U13.3, U14.1
INPUT_USBPOWER_5V: C20.1, R17.2, U3.1, U4.4, U8.1, U8.2
NET_U1_6: C7.1, U1.6
NET_U1_14: R4.1, U1.14, U13.4
NET_U1_22: C8.1, C9.1, F1.1, U1.21, U1.22
NET_U1_94: R5.1, U1.94
NET_U1_98: U11.3, U11.4
NET_U2_3: R6.1, U2.3
NET_U2_7: R8.1, U2.7
NET_U7_4: R9.2, R10.1, U7.4
NET_U8_5: R17.1, U8.5
NET_U8_8: R16.1, U8.8
NET_U10_1: R12.1, R13.1, U10.1
NET_U10_3: R14.2, R15.1, U10.3
NET_U10_4: R11.1, U10.4, U13.2
NET_U11_1: R2.1, U11.1, U11.2
PROC_ADC_IN3: U1.26, U14.3
PROC_ADC_IN13: U1.18, U14.2
PROC_SPI1_MISO: U1.31, U2.2
PROC_SPI1_MOSI: U1.32, U2.5
PROC_SPI1_NSS: R7.1, U1.29, U2.1
PROC_SPI1_SCK: U1.30, U2.6
PROC_USB_DM: U1.70, U3.2, U4.3
PROC_USB_DP: U1.71, U3.3, U4.2
VCC_S1_3V7: C15.1, C16.1, C21.1, U7.5, U7.8, U8.3, U8.4, U9.1
VCC_TIER1_3V3: C1.1, C2.1, C3.1, C4.1, C5.1, C6.1, C10.1, C13.1, C14.1, C17.1, C18.1, C19.1, C22.1, F1.2, R4.2, R6.2, R7.2, R8.2, R9.1, R11.2, R12.2, R14.1, U1.28, U1.50, U1.73, U1.75, U1.100, U2.8, U6.4, U7.1, U10.6, U13.5
